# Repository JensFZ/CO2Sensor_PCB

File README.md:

# CO2Sensor - PCB

## Disclamer 
I've ordered the PCB but i din't recieved it yet.
And I'm not responsible for any damage.

## What's it
PCB of a CO2 Sensor based on the following idea: [Reichelt Magazin - CO2 Sensor](https://www.reichelt.de/magazin/reichelt-magazin/co2-messgeraet-einfach-und-guenstig-selber-bauen/)

Added external power suply, leds and a buzzer (all of them are optional)

## Firmware
comming soon.
The one in the Reichelt Magazin link above should work.

## Tools needed
- soldering iron
- solder

## Part list:

### Necessary parts
- 1x [Joy-IT NodeMCU ESP32 WiFi & Bluetooth](https://www.reichelt.de/nodemcu-esp32-wifi-und-bluetooth-modul-debo-jt-esp32-p219897.html)
- 1x [CO2 MH-Z19C-PH](https://www.reichelt.de/infrarot-co2-sensor-mh-z19c-pinleiste-rm-2-54-co2-mh-z19c-ph-p297320.html)
- 1x [DHT22](https://www.reichelt.de/entwicklerboards-temperatur-feuchtigkeitssensor-dht22-debo-dht-22-p224218.html)
- 1x [4.7 kOhm Resistor](https://www.reichelt.de/widerstand-kohleschicht-4-7-kohm-0207-250-mw-5--1-4w-4-7k-p1425.html)

### Optional parts
#### CASE ####
- [Kleingehäuse 135x95x45mm](https://www.reichelt.de/kleingehaeuse-135-x-95-x-45-mm-eurobox-ge-p50432.html)
- 4x [M3x10 screws](https://www.reichelt.de/pan-head-schrauben-kreuzschlitz-pzd-m3-10mm-skl-m3x10-50-p65753.html?&trstct=pos_12)

#### LEDs ####
- 3x [220 Ohm Resistor](https://www.reichelt.de/widerstand-kohleschicht-220-ohm-0207-250-mw-5--1-4w-220-p1382.html)
- 1x [Green LED](https://www.reichelt.de/led-3-mm-bedrahtet-gruen-125-mcd-40--evl-264-7sygt-p230811.html)
- 1x [Yellow LED](https://www.reichelt.de/led-3-mm-bedrahtet-gelb-200-mcd-40--evl-204-10uyd-p230798.html)
- 1x [Red LED](https://www.reichelt.de/led-3-mm-bedrahtet-rot-125-mcd-60--evl-264-10surd-p230801.html)

#### Buzzer ####
- 1x [12mm Buzzer](https://www.reichelt.de/12-mm-magnetischer-buzzer-vis-3590-p248314.html)
- optional 1x [220 Ohm Resistor](https://www.reichelt.de/widerstand-kohleschicht-220-ohm-0207-250-mw-5--1-4w-220-p1382.html)

#### External Power ####
- 1x [Screw terminal block](https://www.reichelt.de/anschlussklemme-2-pol-1-5-mm-rm-3-5-akl-059-02-p36598.html)

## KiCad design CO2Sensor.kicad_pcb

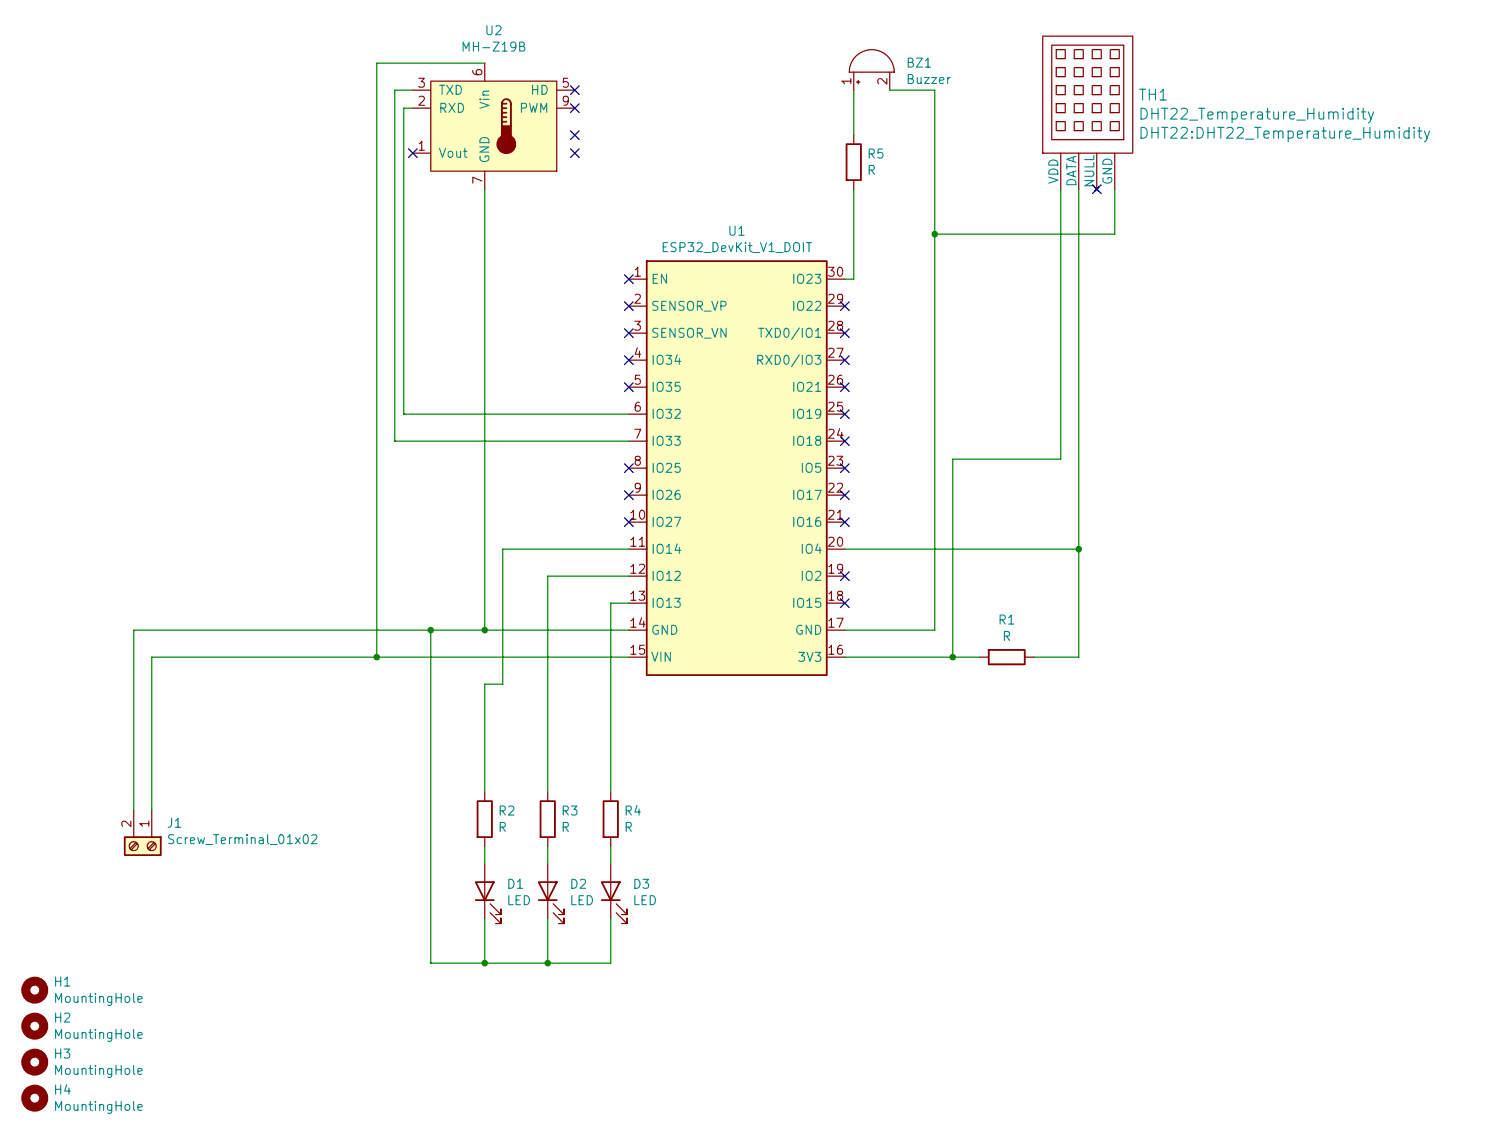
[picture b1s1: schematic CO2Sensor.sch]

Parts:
BZ1: Buzzer; Buzzer_12x9.5RM7.6
D1, D2, D3: LED; LED_D3.0mm
H1, H2, H3, H4: MountingHole; MountingHole_3.2mm_M3_DIN965
J1: Screw_Terminal_01x02; TerminalBlock_MetzConnect_Type059_RT06302HBWC_1x02_P3.50mm_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
R1, R2, R3, R4, R5: R; R_Axial_DIN0207_L6.3mm_D2.5mm_P7.62mm_Horizontal
TH1: DHT22_Temperature_Humidity
U1: ESP32_DevKit_V1_DOIT; esp32_devkit_v1_doit
U2: MH-Z19B; Winsen_MH-Z19B

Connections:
unnamed: BZ1.1 (-), R5.1
unnamed: BZ1.2 (+), TH1.4 (GND), U1.17 (GND)
unnamed: D1.1 (K), D2.1 (K), D3.1 (K), J1.2, U1.14 (GND), U2.7 (GND)
unnamed: D1.2 (A), R2.2
unnamed: D2.2 (A), R3.2
unnamed: D3.2 (A), R4.2
unnamed: J1.1, U1.15 (VIN), U2.6 (Vin)
unnamed: R1.1, TH1.2 (DATA), U1.20 (IO4)
unnamed: R1.2, TH1.1 (VDD), U1.16 (3V3)
unnamed: R2.1, U1.11 (IO14)
unnamed: R3.1, U1.12 (IO12)
unnamed: R4.1, U1.13 (IO13)
unnamed: R5.2, U1.30 (IO23)
unnamed: U1.6 (IO32), U2.2 (RXD)
unnamed: U1.7 (IO33), U2.3 (TXD)

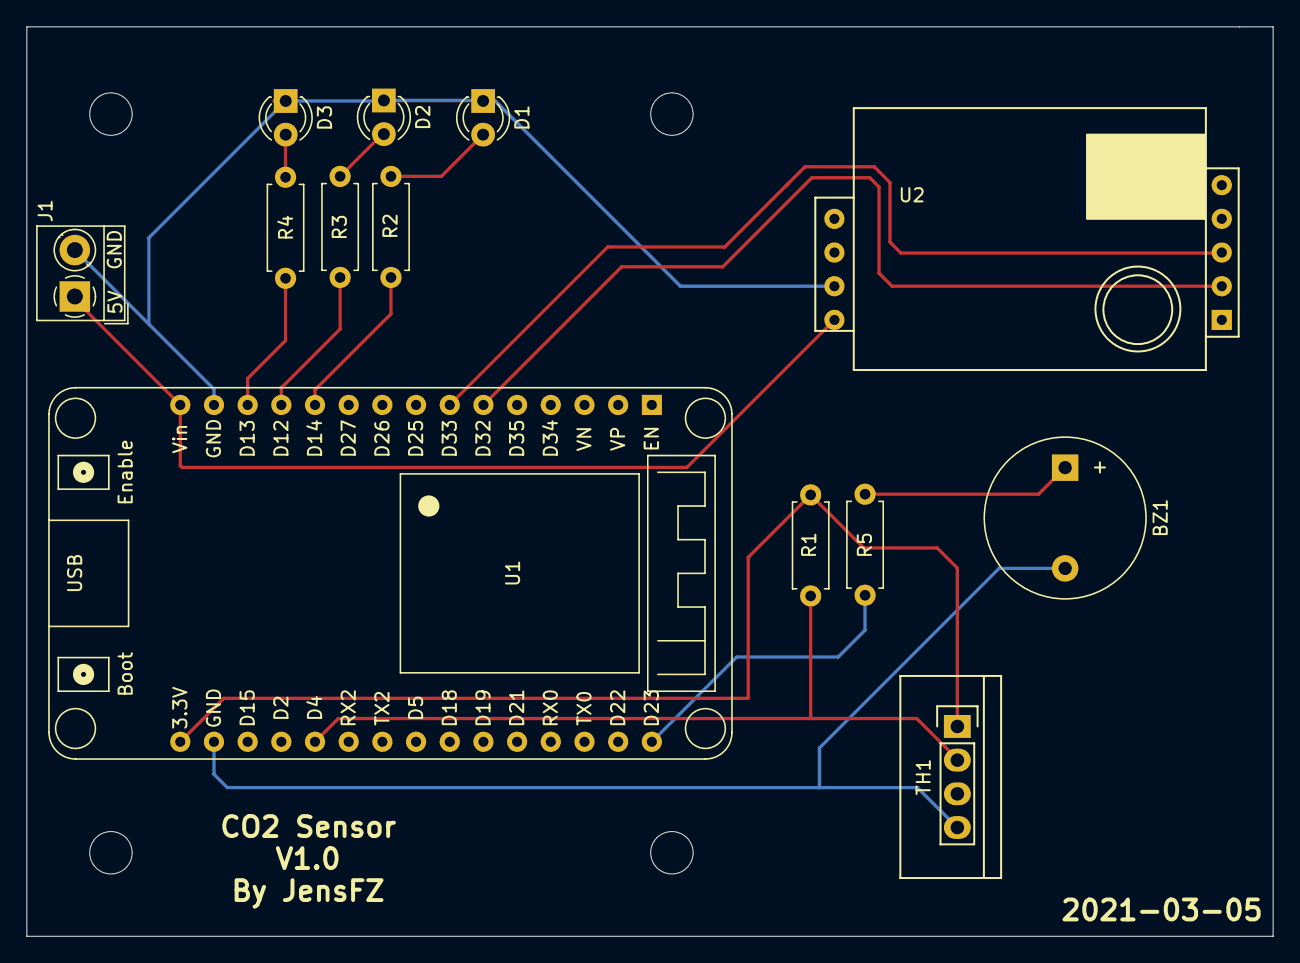
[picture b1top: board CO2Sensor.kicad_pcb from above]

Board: 2 copper layers, 94.0 x 68.6 mm, 17 parts (0 on the bottom side), 15 nets.

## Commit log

2021-03-06 gitignore added
2021-03-06 Rotate KiCAD Logo
2021-03-09 added components description
2021-03-09 added screws
2021-03-09 added Link
2021-05-12 Scad file added
2021-10-14 Bilder der fertigen Platine hinzugefügt
2021-10-14 Gehäuse erstellt - WIP!
2022-03-06 Code hinzugefügt
